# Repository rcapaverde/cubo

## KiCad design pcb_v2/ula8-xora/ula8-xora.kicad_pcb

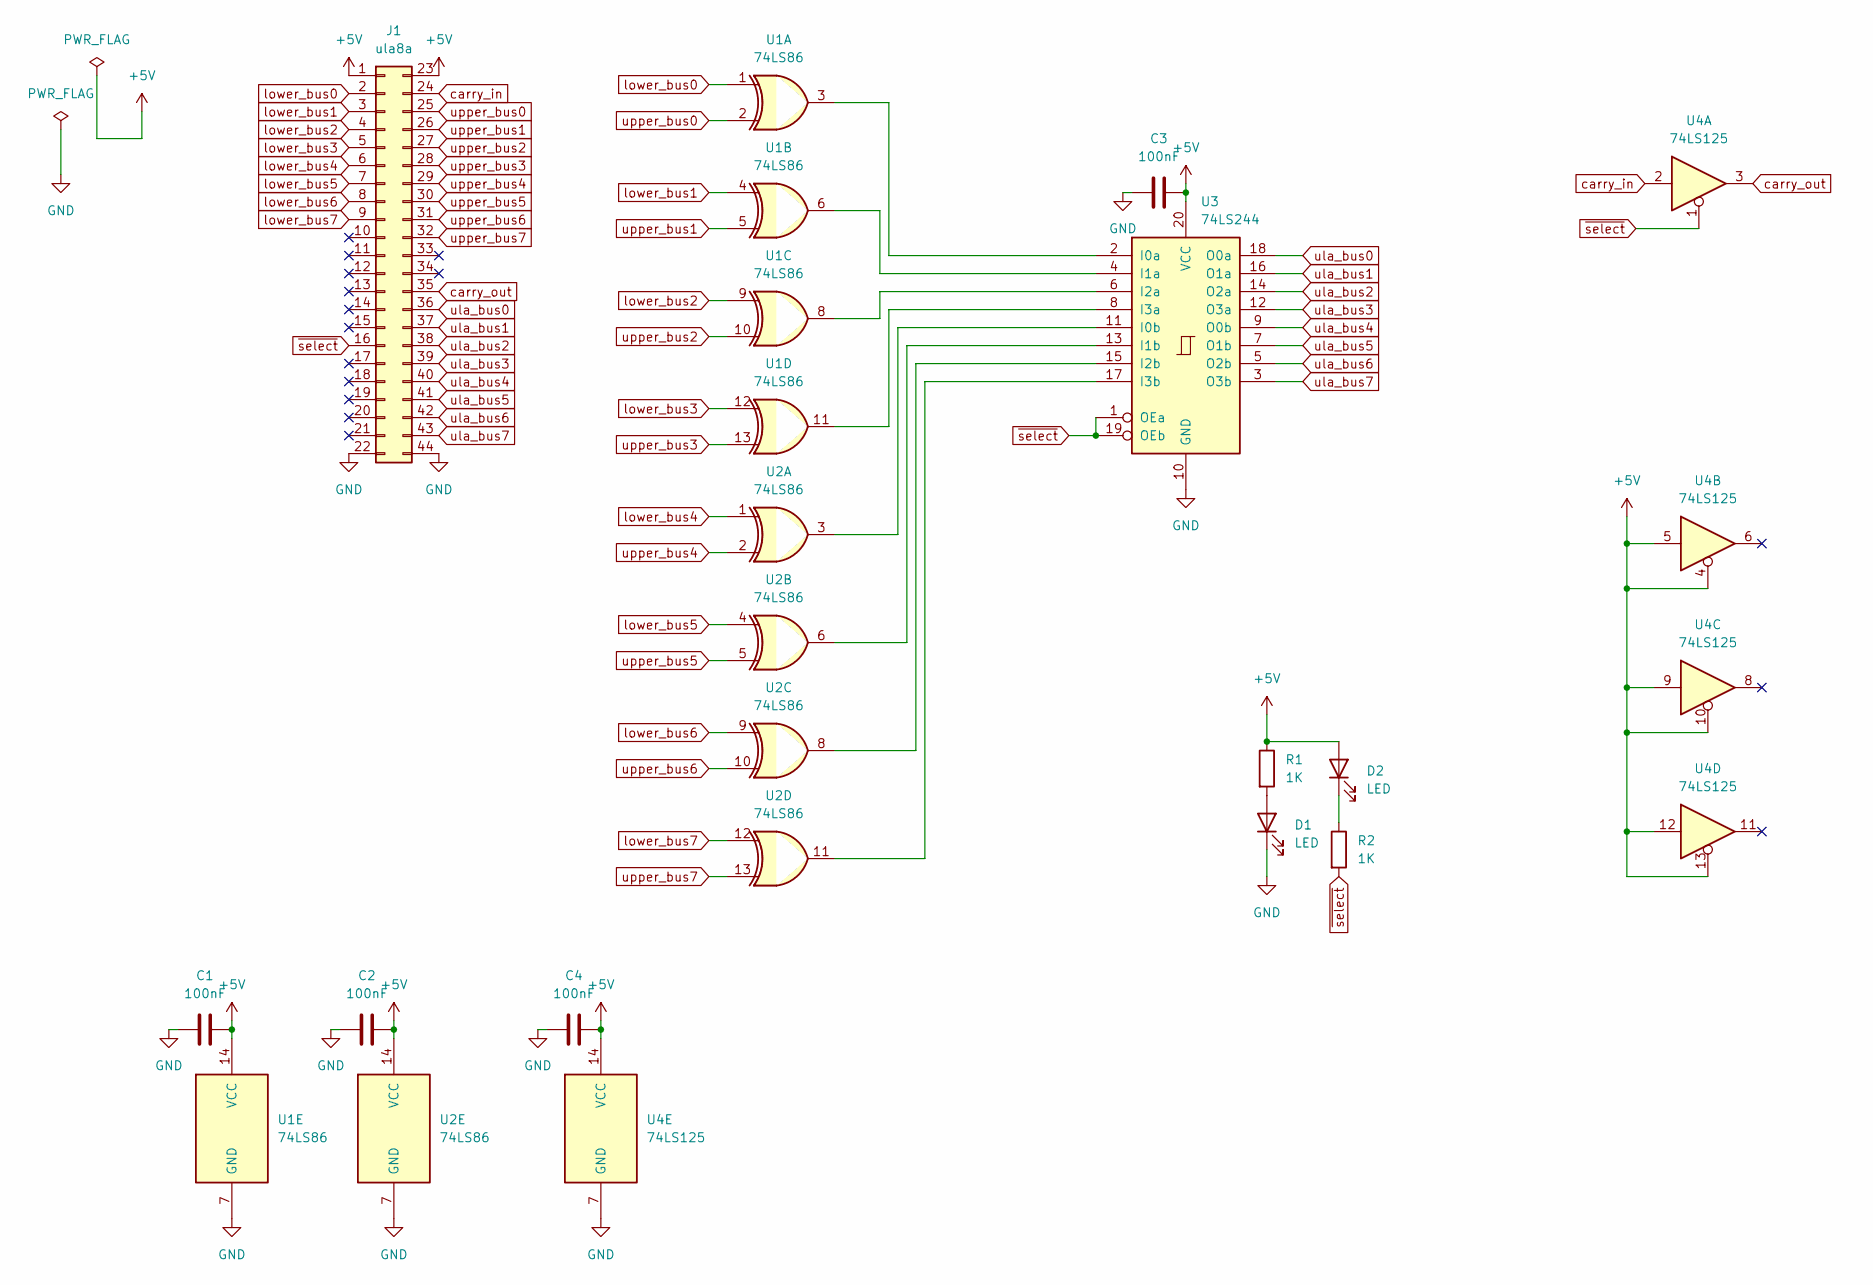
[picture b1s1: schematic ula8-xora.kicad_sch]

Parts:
C1, C2, C3, C4: 100nF; C_Disc_D5.1mm_W3.2mm_P5.00mm
D1, D2: LED; LED_D5.0mm
J1: ula8a; edge-connector-44
R1, R2: 1K; R_Axial_DIN0207_L6.3mm_D2.5mm_P7.62mm_Horizontal
U1, U2: 74LS86; DIP-14_W7.62mm
U3: 74LS244; DIP-20_W7.62mm
U4: 74LS125; DIP-14_W7.62mm

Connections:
+5V: C1.2, C2.2, C3.2, C4.2, D2.2 (A), J1.1, J1.23, R1.1, U1.14 (VCC), U2.14 (VCC), U3.20 (VCC), U4.4, U4.5, U4.9, U4.10, U4.12, U4.13, U4.14 (VCC)
GND: C1.1, C2.1, C3.1, C4.1, D1.1 (K), J1.22, J1.44, U1.7 (GND), U2.7 (GND), U3.10 (GND), U4.7 (GND)
unnamed: D1.2 (A), R1.2
unnamed: D2.1 (K), R2.1
unnamed: U1.3, U3.2 (I0a)
unnamed: U2.3, U3.11 (I0b)
unnamed: U1.6, U3.4 (I1a)
unnamed: U2.6, U3.13 (I1b)
unnamed: U1.8, U3.6 (I2a)
unnamed: U2.8, U3.15 (I2b)
unnamed: U1.11, U3.8 (I3a)
unnamed: U2.11, U3.17 (I3b)
carry_in: J1.24, U4.2
carry_out: J1.35, U4.3
lower_bus0: J1.2, U1.1
lower_bus1: J1.3, U1.4
lower_bus2: J1.4, U1.9
lower_bus3: J1.5, U1.12
lower_bus4: J1.6, U2.1
lower_bus5: J1.7, U2.4
lower_bus6: J1.8, U2.9
lower_bus7: J1.9, U2.12
ula_bus0: J1.36, U3.18 (O0a)
ula_bus1: J1.37, U3.16 (O1a)
ula_bus2: J1.38, U3.14 (O2a)
ula_bus3: J1.39, U3.12 (O3a)
ula_bus4: J1.40, U3.9 (O0b)
ula_bus5: J1.41, U3.7 (O1b)
ula_bus6: J1.42, U3.5 (O2b)
ula_bus7: J1.43, U3.3 (O3b)
upper_bus0: J1.25, U1.2
upper_bus1: J1.26, U1.5
upper_bus2: J1.27, U1.10
upper_bus3: J1.28, U1.13
upper_bus4: J1.29, U2.2
upper_bus5: J1.30, U2.5
upper_bus6: J1.31, U2.10
upper_bus7: J1.32, U2.13
~select: J1.16, R2.2, U3.1 (OEa), U3.19 (OEb), U4.1

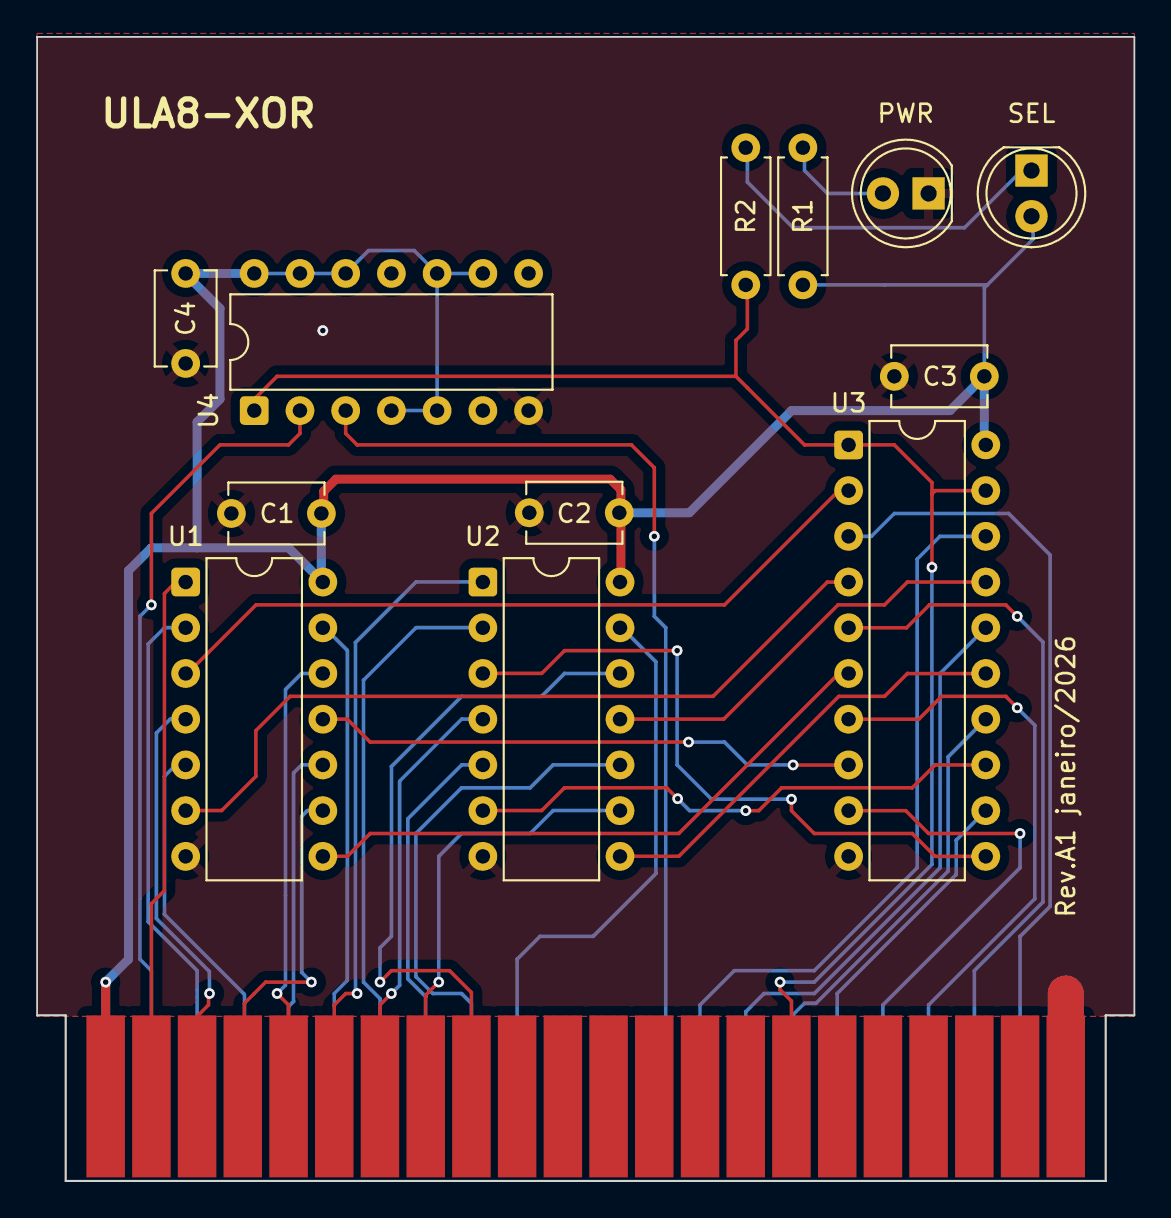
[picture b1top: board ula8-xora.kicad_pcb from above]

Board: 2 copper layers, 61.0 x 63.6 mm, 13 parts (0 on the bottom side), 39 nets.

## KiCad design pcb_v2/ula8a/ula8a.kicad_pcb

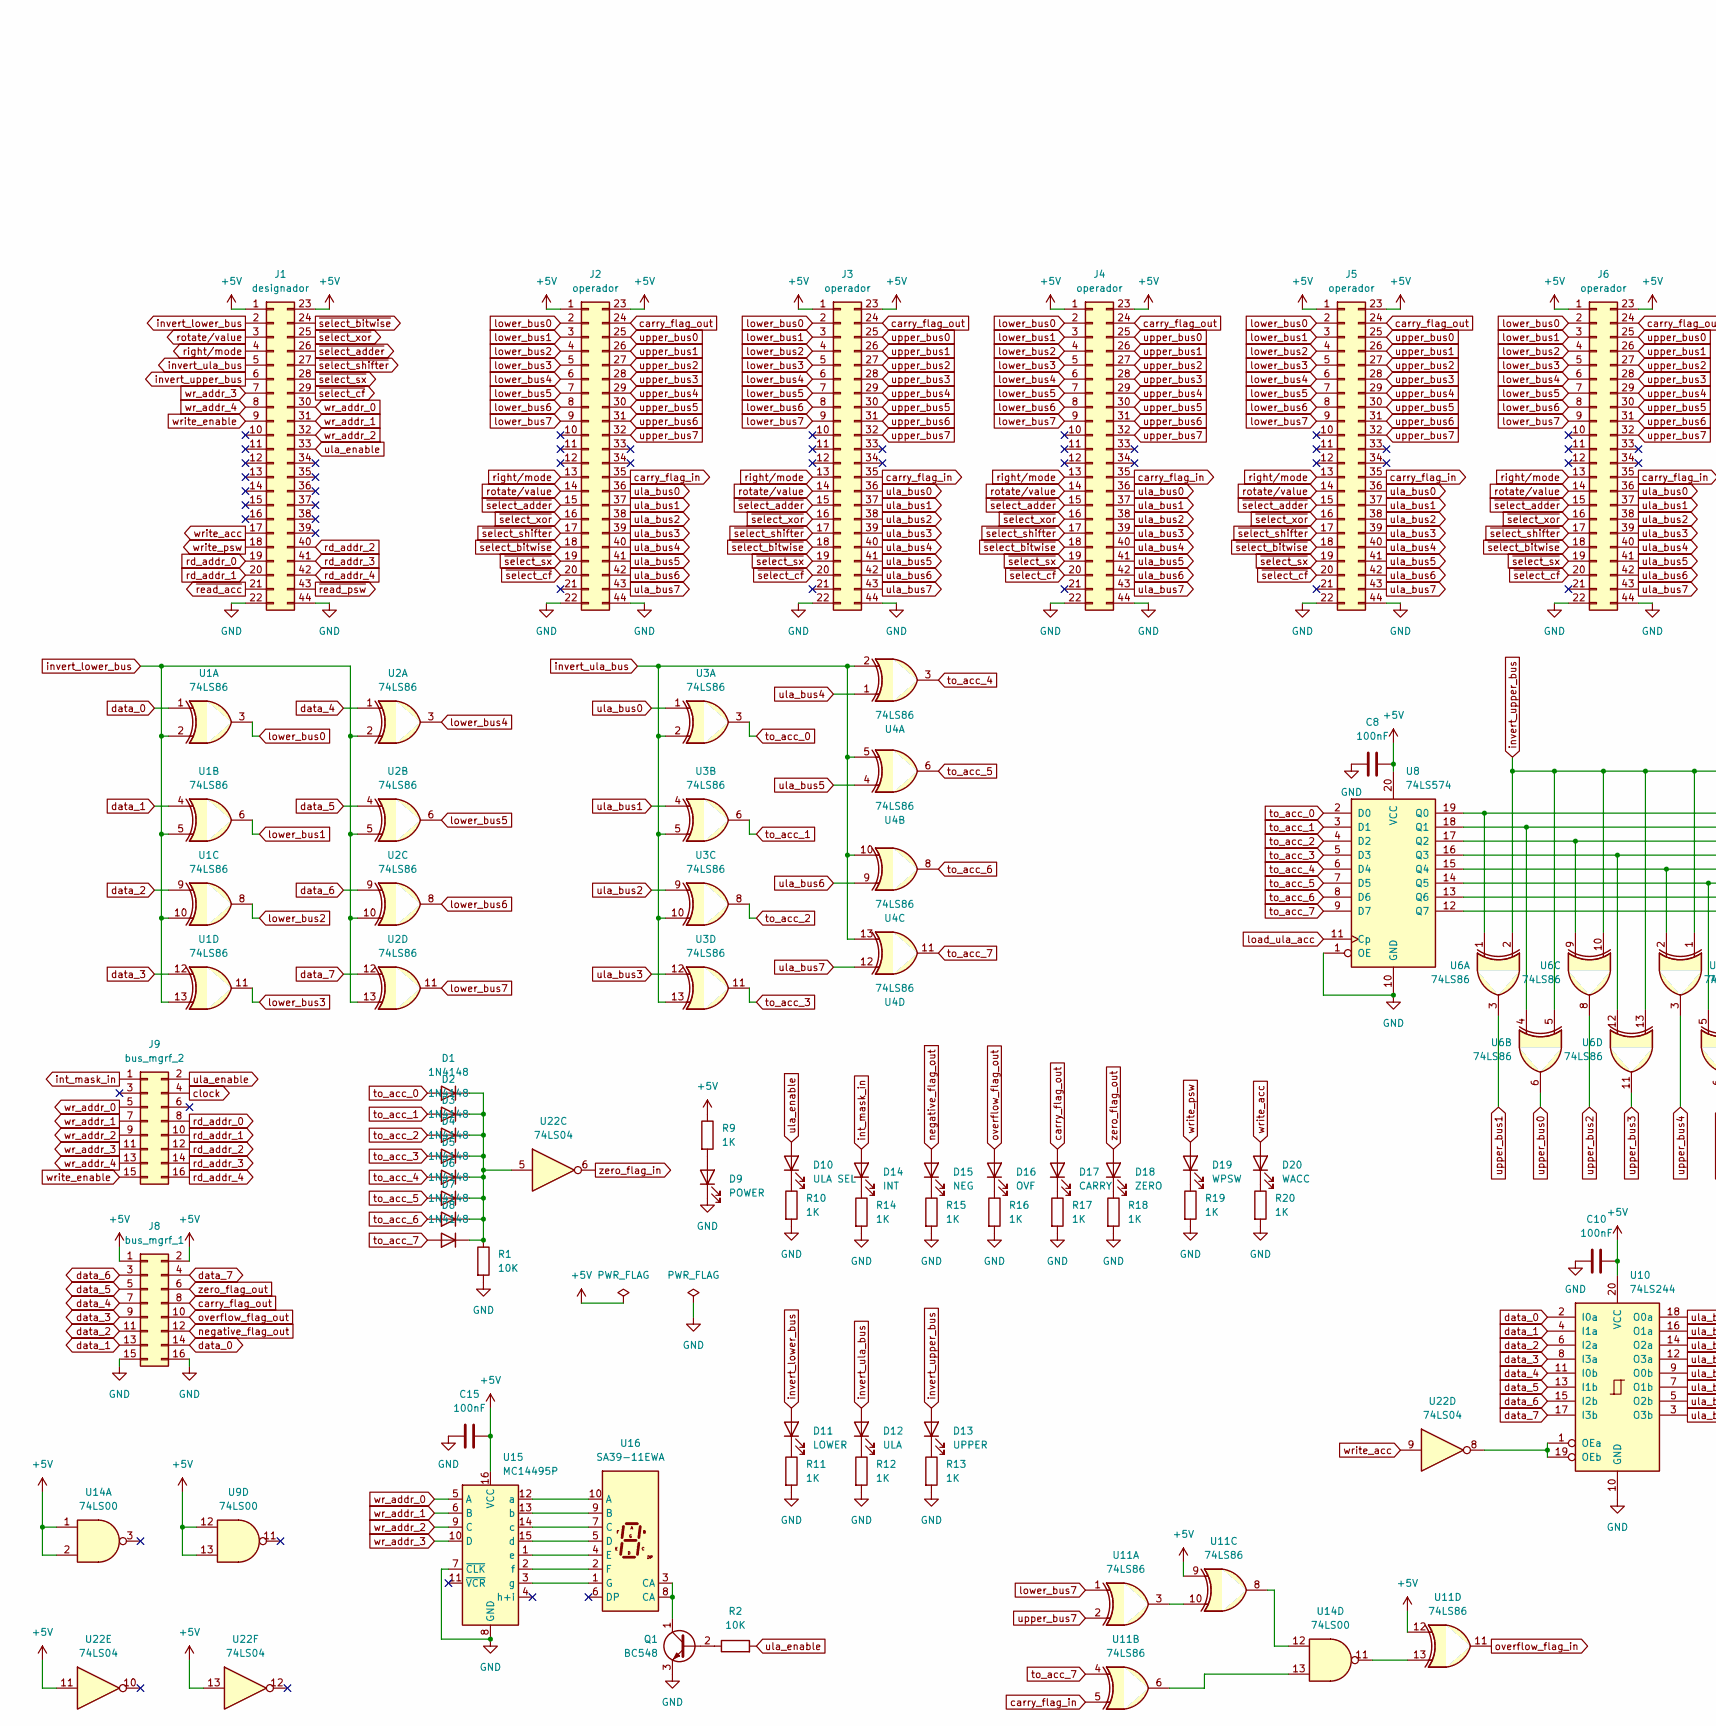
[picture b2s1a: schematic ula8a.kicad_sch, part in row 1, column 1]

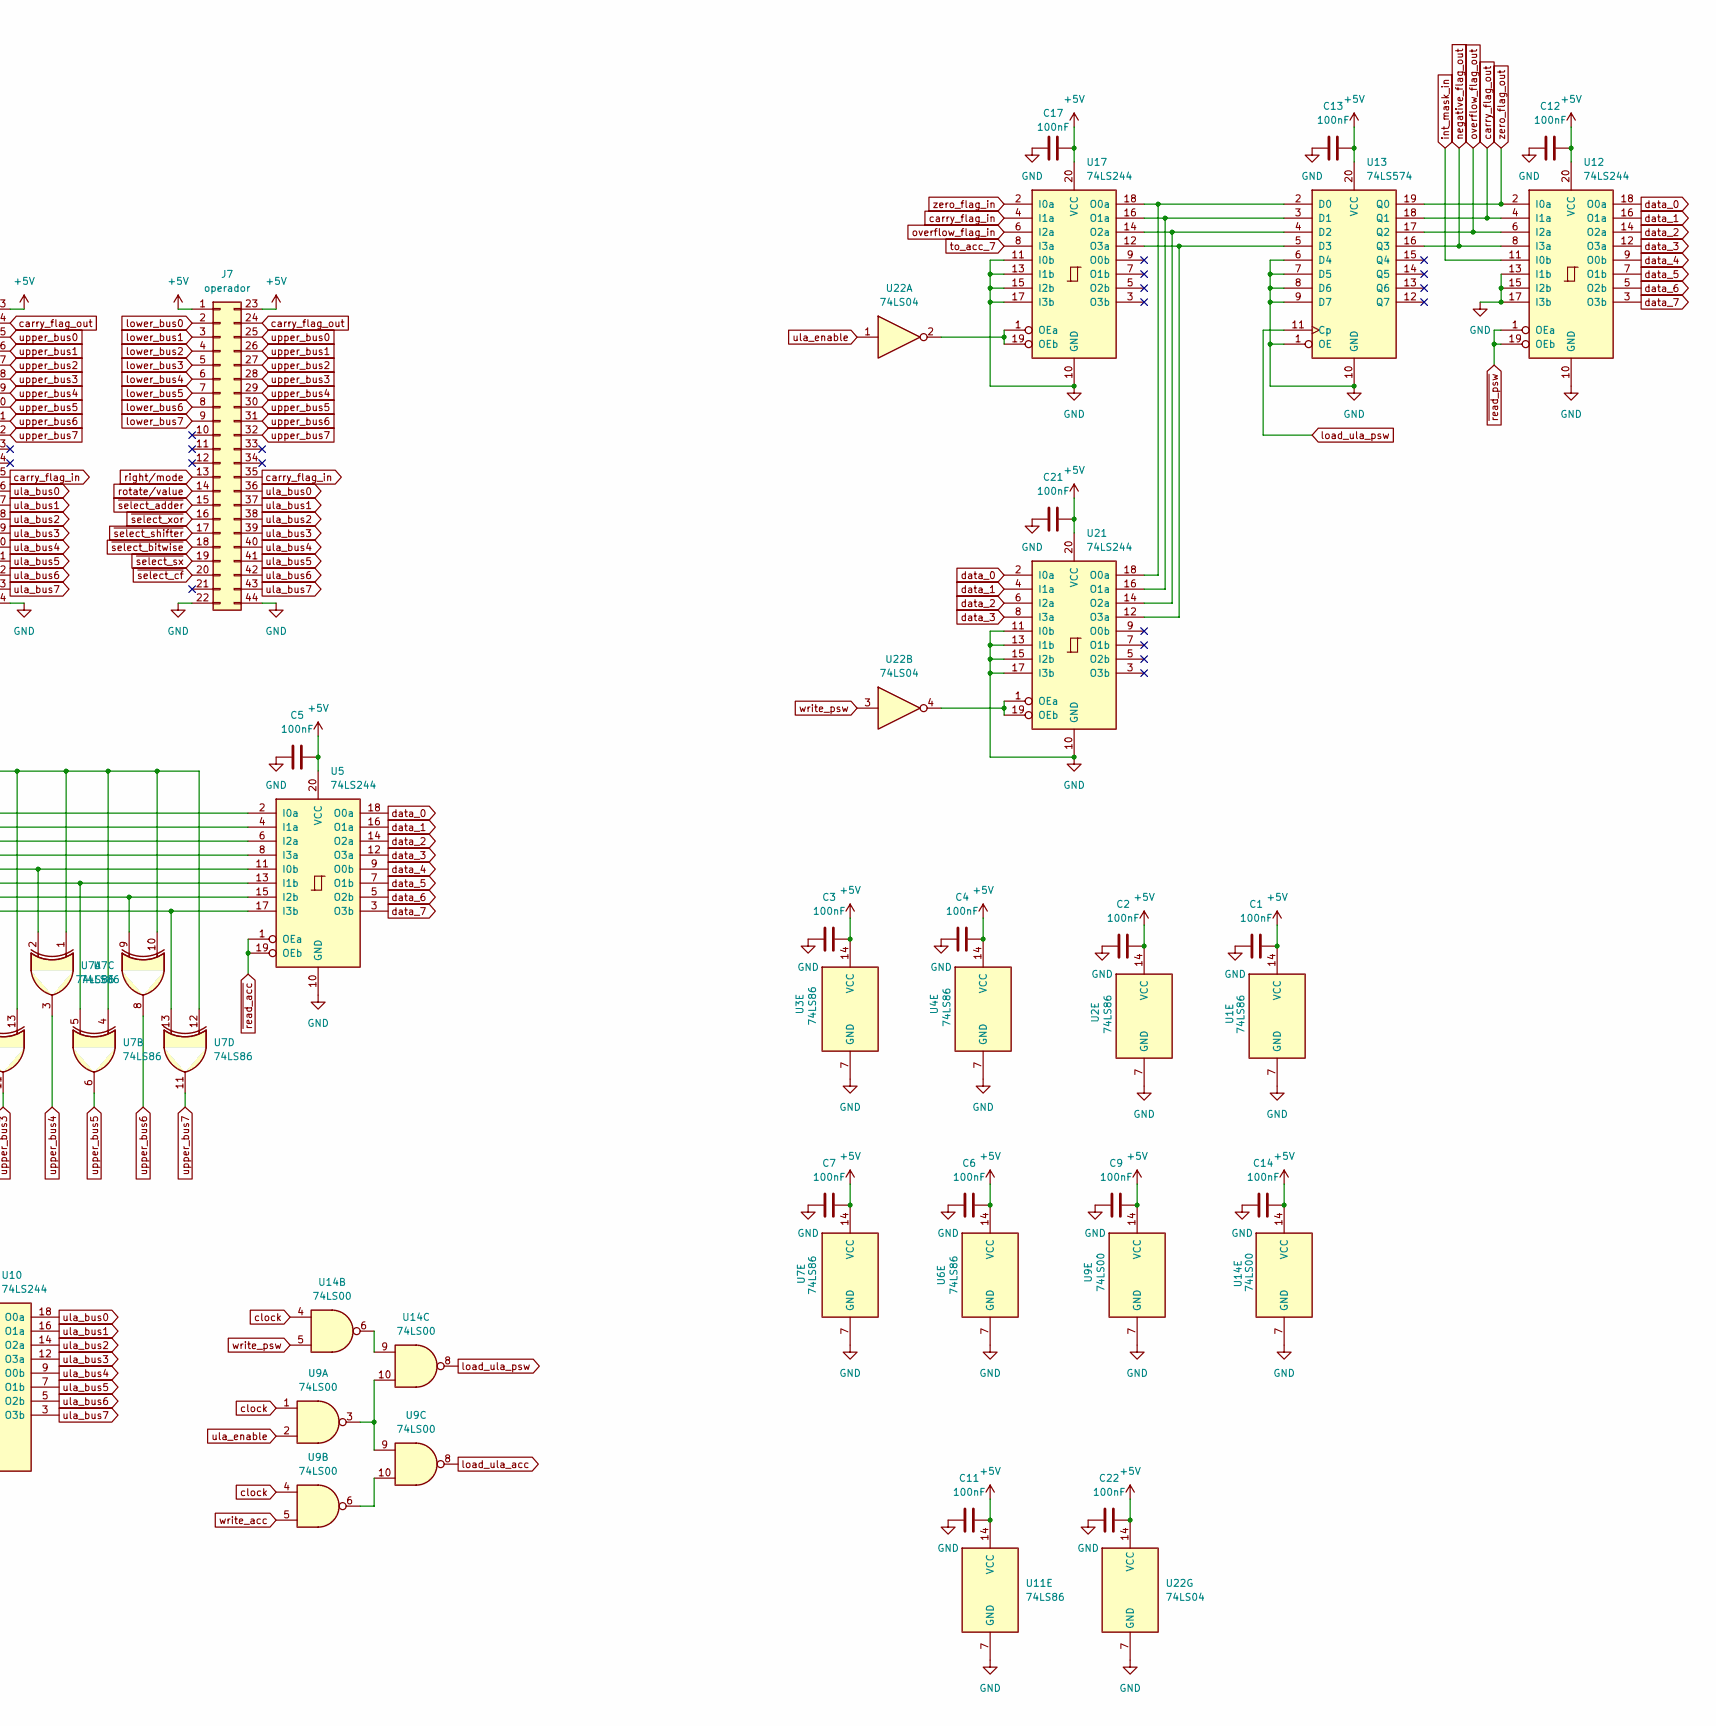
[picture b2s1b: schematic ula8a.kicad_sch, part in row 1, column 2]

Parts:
C1, C2, C3, C4, C5, C6, C7, C8, C9, C10, C11, C12, C13, C14, C15, C17, C21, C22: 100nF; C_Disc_D5.1mm_W3.2mm_P5.00mm
D1, D2, D3, D4, D5, D6, D7, D8: 1N4148; D_DO-35_SOD27_P7.62mm_Horizontal
D9: POWER; LED_D5.0mm
D10: ULA SEL; LED_D5.0mm
D11: LOWER; LED_D5.0mm
D12: ULA; LED_D5.0mm
D13: UPPER; LED_D5.0mm
D14: INT; LED_D5.0mm
D15: NEG; LED_D5.0mm
D16: OVF; LED_D5.0mm
D17: CARRY; LED_D5.0mm
D18: ZERO; LED_D5.0mm
D19: WPSW; LED_D5.0mm
D20: WACC; LED_D5.0mm
J1: designador; male-edge-connector-44
J2, J3, J4, J5, J6, J7: operador; male-edge-connector-44
J8: bus_mgrf_1; conector 02x08
J9: bus_mgrf_2; conector 02x08
Q1: BC548; TO-92_Inline
R1, R2: 10K; R_Axial_DIN0207_L6.3mm_D2.5mm_P7.62mm_Horizontal
R9, R10, R11, R12, R13, R14, R15, R16, R17, R18, R19, R20: 1K; R_Axial_DIN0207_L6.3mm_D2.5mm_P7.62mm_Horizontal
U1, U2, U3, U4, U6, U7, U11: 74LS86; DIP-14_W7.62mm
U5, U10, U12, U17, U21: 74LS244; DIP-20_W7.62mm
U8, U13: 74LS574; DIP-20_W7.62mm
U9, U14: 74LS00; DIP-14_W7.62mm
U15: MC14495P; DIP-16_W7.62mm
U16: SA39-11EWA; 1-digit-13mm
U22: 74LS04; DIP-14_W7.62mm

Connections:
+5V: C1.2, C2.2, C3.2, C4.2, C5.2, C6.2, C7.2, C8.2, C9.2, C10.2, C11.2, C12.2, C13.2, C14.2, C15.2, C17.2, C21.2, C22.2, J1.1, J1.23, J2.1, J2.23, J3.1, J3.23, J4.1, J4.23, J5.1, J5.23, J6.1, J6.23, J7.1, J7.23, J8.1, J8.2, R9.1, U1.14 (VCC), U2.14 (VCC), U3.14 (VCC), U4.14 (VCC), U5.20 (VCC), U6.14 (VCC), U7.14 (VCC), U8.20 (VCC), U9.12, U9.13, U9.14 (VCC), U10.20 (VCC), U11.9, U11.12, U11.14 (VCC), U12.20 (VCC), U13.20 (VCC), U14.1, U14.2, U14.14 (VCC), U15.16 (VCC), U17.20 (VCC), U21.20 (VCC), U22.11, U22.13, U22.14 (VCC)
GND: C1.1, C2.1, C3.1, C4.1, C5.1, C6.1, C7.1, C8.1, C9.1, C10.1, C11.1, C12.1, C13.1, C14.1, C15.1, C17.1, C21.1, C22.1, D9.1 (K), J1.22, J1.44, J2.22, J2.44, J3.22, J3.44, J4.22, J4.44, J5.22, J5.44, J6.22, J6.44, J7.22, J7.44, J8.15, J8.16, Q1.3 (E), R1.2, R10.2, R11.2, R12.2, R13.2, R14.2, R15.2, R16.2, R17.2, R18.2, R19.2, R20.2, U1.7 (GND), U2.7 (GND), U3.7 (GND), U4.7 (GND), U5.10 (GND), U6.7 (GND), U7.7 (GND), U8.1 (OE), U8.10 (GND), U9.7 (GND), U10.10 (GND), U11.7 (GND), U12.10 (GND), U12.13 (I1b), U12.15 (I2b), U12.17 (I3b), U13.1 (OE), U13.6 (D4), U13.7 (D5), U13.8 (D6), U13.9 (D7), U13.10 (GND), U14.7 (GND), U15.7 (~CLK), U15.8 (GND), U17.10 (GND), U17.11 (I0b), U17.13 (I1b), U17.15 (I2b), U17.17 (I3b), U21.10 (GND), U21.11 (I0b), U21.13 (I1b), U21.15 (I2b), U21.17 (I3b), U22.7 (GND)
unnamed: D1.1 (K), D2.1 (K), D3.1 (K), D4.1 (K), D5.1 (K), D6.1 (K), D7.1 (K), D8.1 (K), R1.1, U22.5
unnamed: D9.2 (A), R9.2
unnamed: D10.1 (K), R10.1
unnamed: D11.1 (K), R11.1
unnamed: D12.1 (K), R12.1
unnamed: D13.1 (K), R13.1
unnamed: D14.1 (K), R14.1
unnamed: D15.1 (K), R15.1
unnamed: D16.1 (K), R16.1
unnamed: D17.1 (K), R17.1
unnamed: D18.1 (K), R18.1
unnamed: D19.1 (K), R19.1
unnamed: D20.1 (K), R20.1
unnamed: Q1.2 (B), R2.1
unnamed: Q1.1 (C), U16.3 (CA), U16.8 (CA)
unnamed: U5.2 (I0a), U6.1, U8.19 (Q0)
unnamed: U5.11 (I0b), U7.2, U8.15 (Q4)
unnamed: U5.4 (I1a), U6.4, U8.18 (Q1)
unnamed: U5.13 (I1b), U7.5, U8.14 (Q5)
unnamed: U5.6 (I2a), U6.9, U8.17 (Q2)
unnamed: U5.15 (I2b), U7.9, U8.13 (Q6)
unnamed: U5.8 (I3a), U6.12, U8.16 (Q3)
unnamed: U5.17 (I3b), U7.13, U8.12 (Q7)
unnamed: U9.6, U9.10
unnamed: U10.1 (OEa), U10.19 (OEb), U22.8
unnamed: U11.6, U14.13
unnamed: U11.8, U14.12
unnamed: U11.3, U11.10
unnamed: U11.13, U14.11
unnamed: U13.2 (D0), U17.18 (O0a), U21.18 (O0a)
unnamed: U13.3 (D1), U17.16 (O1a), U21.16 (O1a)
unnamed: U13.4 (D2), U17.14 (O2a), U21.14 (O2a)
unnamed: U13.5 (D3), U17.12 (O3a), U21.12 (O3a)
unnamed: U14.6, U14.9
unnamed: U9.3, U9.9, U14.10
unnamed: U15.12 (a), U16.10 (A)
unnamed: U15.13 (b), U16.9 (B)
unnamed: U15.14 (c), U16.7 (C)
unnamed: U15.15 (d), U16.5 (D)
unnamed: U15.1 (e), U16.4 (E)
unnamed: U15.2 (f), U16.2 (F)
unnamed: U15.3 (g), U16.1 (G)
unnamed: U17.1 (OEa), U17.19 (OEb), U22.2
unnamed: U21.1 (OEa), U21.19 (OEb), U22.4
carry_flag_in: J2.35, J3.35, J4.35, J5.35, J6.35, J7.35, U11.5, U17.4 (I1a)
carry_flag_out: D17.2 (A), J2.24, J3.24, J4.24, J5.24, J6.24, J7.24, J8.8, U12.4 (I1a), U13.18 (Q1)
clock: J9.4, U9.1, U9.4, U14.4
data_0: J8.14, U1.1, U5.18 (O0a), U10.2 (I0a), U12.18 (O0a), U21.2 (I0a)
data_1: J8.13, U1.4, U5.16 (O1a), U10.4 (I1a), U12.16 (O1a), U21.4 (I1a)
data_2: J8.11, U1.9, U5.14 (O2a), U10.6 (I2a), U12.14 (O2a), U21.6 (I2a)
data_3: J8.9, U1.12, U5.12 (O3a), U10.8 (I3a), U12.12 (O3a), U21.8 (I3a)
data_4: J8.7, U2.1, U5.9 (O0b), U10.11 (I0b), U12.9 (O0b)
data_5: J8.5, U2.4, U5.7 (O1b), U10.13 (I1b), U12.7 (O1b)
data_6: J8.3, U2.9, U5.5 (O2b), U10.15 (I2b), U12.5 (O2b)
data_7: J8.4, U2.12, U5.3 (O3b), U10.17 (I3b), U12.3 (O3b)
int_mask_in: D14.2 (A), J9.1, U12.11 (I0b)
invert_lower_bus: D11.2 (A), J1.2, U1.2, U1.5, U1.10, U1.13, U2.2, U2.5, U2.10, U2.13
invert_ula_bus: D12.2 (A), J1.5, U3.2, U3.5, U3.10, U3.13, U4.2, U4.5, U4.10, U4.13
invert_upper_bus: D13.2 (A), J1.6, U6.2, U6.5, U6.10, U6.13, U7.1, U7.4, U7.10, U7.12
load_ula_acc: U8.11 (Cp), U9.8
load_ula_psw: U13.11 (Cp), U14.8
lower_bus0: J2.2, J3.2, J4.2, J5.2, J6.2, J7.2, U1.3
lower_bus1: J2.3, J3.3, J4.3, J5.3, J6.3, J7.3, U1.6
lower_bus2: J2.4, J3.4, J4.4, J5.4, J6.4, J7.4, U1.8
lower_bus3: J2.5, J3.5, J4.5, J5.5, J6.5, J7.5, U1.11
lower_bus4: J2.6, J3.6, J4.6, J5.6, J6.6, J7.6, U2.3
lower_bus5: J2.7, J3.7, J4.7, J5.7, J6.7, J7.7, U2.6
lower_bus6: J2.8, J3.8, J4.8, J5.8, J6.8, J7.8, U2.8
lower_bus7: J2.9, J3.9, J4.9, J5.9, J6.9, J7.9, U2.11, U11.1
negative_flag_out: D15.2 (A), J8.12, U12.8 (I3a), U13.16 (Q3)
overflow_flag_in: U11.11, U17.6 (I2a)
overflow_flag_out: D16.2 (A), J8.10, U12.6 (I2a), U13.17 (Q2)
rd_addr_0: J1.19, J9.8
rd_addr_1: J1.20, J9.10
rd_addr_2: J1.40, J9.12
rd_addr_3: J1.41, J9.14
rd_addr_4: J1.42, J9.16
right/mode: J1.4, J2.13, J3.13, J4.13, J5.13, J6.13, J7.13
rotate/value: J1.3, J2.14, J3.14, J4.14, J5.14, J6.14, J7.14
to_acc_0: D1.2 (A), U3.3, U8.2 (D0)
to_acc_1: D2.2 (A), U3.6, U8.3 (D1)
to_acc_2: D3.2 (A), U3.8, U8.4 (D2)
to_acc_3: D4.2 (A), U3.11, U8.5 (D3)
to_acc_4: D5.2 (A), U4.3, U8.6 (D4)
to_acc_5: D6.2 (A), U4.6, U8.7 (D5)
to_acc_6: D7.2 (A), U4.8, U8.8 (D6)
to_acc_7: D8.2 (A), U4.11, U8.9 (D7), U11.4, U17.8 (I3a)
ula_bus0: J2.36, J3.36, J4.36, J5.36, J6.36, J7.36, U3.1, U10.18 (O0a)
ula_bus1: J2.37, J3.37, J4.37, J5.37, J6.37, J7.37, U3.4, U10.16 (O1a)
ula_bus2: J2.38, J3.38, J4.38, J5.38, J6.38, J7.38, U3.9, U10.14 (O2a)
ula_bus3: J2.39, J3.39, J4.39, J5.39, J6.39, J7.39, U3.12, U10.12 (O3a)
ula_bus4: J2.40, J3.40, J4.40, J5.40, J6.40, J7.40, U4.1, U10.9 (O0b)
ula_bus5: J2.41, J3.41, J4.41, J5.41, J6.41, J7.41, U4.4, U10.7 (O1b)
ula_bus6: J2.42, J3.42, J4.42, J5.42, J6.42, J7.42, U4.9, U10.5 (O2b)
ula_bus7: J2.43, J3.43, J4.43, J5.43, J6.43, J7.43, U4.12, U10.3 (O3b)
ula_enable: D10.2 (A), J1.33, J9.2, R2.2, U9.2, U22.1
upper_bus0: J2.25, J3.25, J4.25, J5.25, J6.25, J7.25, U6.6
upper_bus1: J2.26, J3.26, J4.26, J5.26, J6.26, J7.26, U6.3
upper_bus2: J2.27, J3.27, J4.27, J5.27, J6.27, J7.27, U6.8
upper_bus3: J2.28, J3.28, J4.28, J5.28, J6.28, J7.28, U6.11
upper_bus4: J2.29, J3.29, J4.29, J5.29, J6.29, J7.29, U7.3
upper_bus5: J2.30, J3.30, J4.30, J5.30, J6.30, J7.30, U7.6
upper_bus6: J2.31, J3.31, J4.31, J5.31, J6.31, J7.31, U7.8
upper_bus7: J2.32, J3.32, J4.32, J5.32, J6.32, J7.32, U7.11, U11.2
wr_addr_0: J1.30, J9.5, U15.5 (A)
wr_addr_1: J1.31, J9.7, U15.6 (B)
wr_addr_2: J1.32, J9.9, U15.9 (C)
wr_addr_3: J1.7, J9.11, U15.10 (D)
wr_addr_4: J1.8, J9.13
write_acc: D20.2 (A), J1.17, U9.5, U22.9
write_enable: J1.9, J9.15
write_psw: D19.2 (A), J1.18, U14.5, U22.3
zero_flag_in: U17.2 (I0a), U22.6
zero_flag_out: D18.2 (A), J8.6, U12.2 (I0a), U13.19 (Q0)
~read_acc: J1.21, U5.1 (OEa), U5.19 (OEb)
~read_psw: J1.43, U12.1 (OEa), U12.19 (OEb)
~select_adder: J1.26, J2.15, J3.15, J4.15, J5.15, J6.15, J7.15
~select_bitwise: J1.24, J2.18, J3.18, J4.18, J5.18, J6.18, J7.18
~select_cf: J1.29, J2.20, J3.20, J4.20, J5.20, J6.20, J7.20
~select_shifter: J1.27, J2.17, J3.17, J4.17, J5.17, J6.17, J7.17
~select_sx: J1.28, J2.19, J3.19, J4.19, J5.19, J6.19, J7.19
~select_xor: J1.25, J2.16, J3.16, J4.16, J5.16, J6.16, J7.16

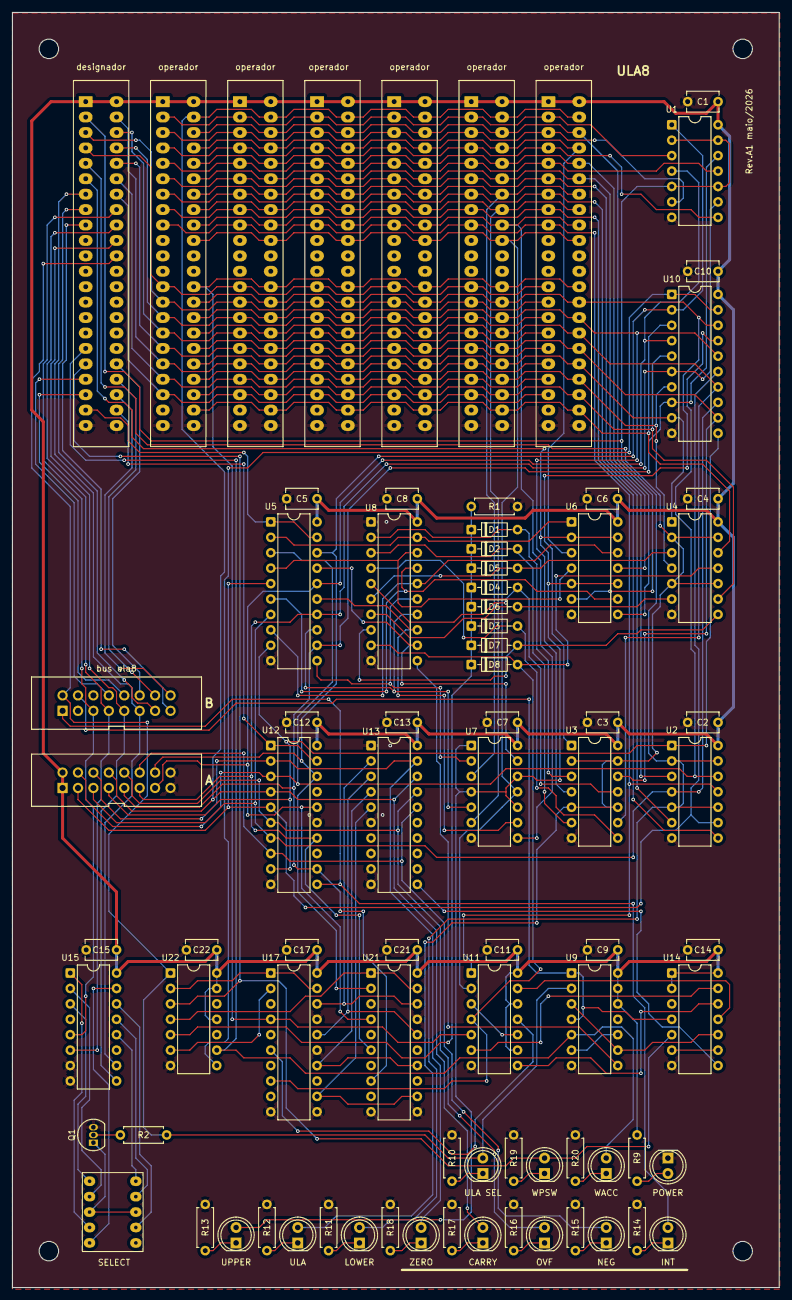
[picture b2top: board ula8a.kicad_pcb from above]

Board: 2 copper layers, 126.3 x 210.0 mm, 81 parts (0 on the bottom side), 124 nets.
